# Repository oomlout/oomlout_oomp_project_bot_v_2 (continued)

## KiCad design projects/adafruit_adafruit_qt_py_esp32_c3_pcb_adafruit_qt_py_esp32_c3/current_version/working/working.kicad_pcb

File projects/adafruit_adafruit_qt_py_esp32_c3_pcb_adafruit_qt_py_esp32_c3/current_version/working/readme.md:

# adafruit_qt_py_esp32_c3_pcb
 
## summary 
* id: adafruit_adafruit_qt_py_esp32_c3_pcb_adafruit_qt_py_esp32_c3
* user: adafruit
* name: adafruit_qt_py_esp32_c3_pcb
* board: adafruit_qt_py_esp32_c3
* repo: https://github.com/adafruit/Adafruit-QT-Py-ESP32-C3-PCB

* src_file_repo_sch: 
* src_file_repo_sch_link: https://github.com/adafruit/Adafruit-QT-Py-ESP32-C3-PCB/tree/main/
* full details link: https://github.com/oomlout/oomlout_oomp_project_bot_v_2/tree/main/projects/adafruit_adafruit_qt_py_esp32_c3_pcb_adafruit_qt_py_esp32_c3/current_version/working  

## schematic  
  
[schematic (pdf)](working_schematic.pdf) 

## pcb  

[board (pdf)](working.pdf)  

## working_bom
| Id | Designator | Footprint | Quantity | Designation | Supplier and ref |  | None | 
| --- | --- | --- | --- | --- | --- | --- | --- | 
| 1 | C8,C1,C6 | 0805-NO | 3 | 22uF |  |  | [''] | 
| 2 | JP3,JP1 | 1X07_CASTEL | 2 |  |  |  | [''] | 
| 3 | Q2 | BTN_KMR2_SLIM | 1 | reset |  |  | [''] | 
| 4 | LED1 | SK6805_1515 | 1 | WS2812B_SK6805_1515 |  |  | [''] | 
| 5 | U1 | SOT23-5 | 1 | AP2112K-3.3 |  |  | [''] | 
| 6 | R5,R6 | _0402NO | 2 | 5.1K |  |  | [''] | 
| 7 | U$3 | QTPYC3_TOP | 1 |  |  |  | [''] | 
| 8 | X6 | USB_C_CUSB31-CFM2AX-01-X | 1 | USB TYPE C |  |  | [''] | 
| 9 | Q1 | BTN_KMR2_4.6X2.8 | 1 | BOOT0 |  |  | [''] | 
| 10 | U$8,U$6 | FIDUCIAL_1MM | 2 | FIDUCIAL_1MM |  |  | [''] | 
| 11 | X1 | ANT_2450AT18B100 | 1 | 2.4GHz |  |  | [''] | 
| 12 | CONN1 | JST_SH4_SKINNY | 1 | STEMMA_I2C_QTSKINNY |  |  | [''] | 
| 13 | C14,C4,C10 | _0402NO | 3 | 0.1uF |  |  | [''] | 
| 14 | GND0 | TESTPOINT_MINUS_1X3MM | 1 |  |  |  | [''] | 
| 15 | C3,C11,C2,C15 | _0402NO | 4 | 1uF |  |  | [''] | 
| 16 | SWC1,SWC2 | B1,27 | 2 | TPB1,27 |  |  | [''] | 
| 17 | L1 | _0402 | 1 | 2nH |  |  | [''] | 
| 18 | R3 | _0402NO | 1 | 0 |  |  | [''] | 
| 19 | R1,R2 | _0402NO | 2 | 10K |  |  | [''] | 
| 20 | VBAT0 | TESTPOINT_PLUS_1X3MM | 1 |  |  |  | [''] | 
| 21 | C16 | _0402NO | 1 | 0.01uF |  |  | [''] | 
| 22 | C18,C17 | _0402NO | 2 | 16pF |  |  | [''] | 
| 23 | Y1 | CRYSTAL_2X1.6 | 1 | 40MHz |  |  | [''] | 
| 24 | L2 | _0402 | 1 | 0 ohm |  |  | [''] | 
| 25 | U$18 | QTPYC3_BOT | 1 |  |  |  | [''] | 
| 26 | U$12 | PCBFEAT-REV-040 | 1 |  |  |  | [''] | 
| 27 | U2 | QFN32_5MM | 1 | ESP32-C3FH4 |  |  | [''] | 
| 28 | D1,D2 | SOD-323_MINI | 2 |   NSR0320 |  |  | [''] | 
| 29 | C9,C7 | _0402NO | 2 | TBD |  |  | [''] | 
| 30 | R7 | _0603MP_TWO6MIL | 1 | 10K |  |  | [''] | 
| 31 | R4 | _0402NO | 1 | 1k |  |  | [''] | 

## bom_schematic
| Ref | Qnty | Value | Cmp name | Footprint | Description | Vendor | DNP | 
| --- | --- | --- | --- | --- | --- | --- | --- | 
| C1, C6, C8 | 3 | 22uF | CAP_CERAMIC0805-NOOUTLINE | working:0805-NO |  |  |  | 
| C2, C3, C11, C15 | 4 | 1uF | CAP_CERAMIC_0402NO | working:_0402NO |  |  |  | 
| C4, C10, C14 | 3 | 0.1uF | CAP_CERAMIC_0402NO | working:_0402NO |  |  |  | 
| C7, C9 | 2 | TBD | CAP_CERAMIC_0402NO | working:_0402NO |  |  |  | 
| C16 | 1 | 0.01uF | CAP_CERAMIC_0402NO | working:_0402NO |  |  |  | 
| C17, C18 | 2 | 16pF | CAP_CERAMIC_0402NO | working:_0402NO |  |  |  | 
| CONN1 | 1 | STEMMA_I2C_QTSKINNY | STEMMA_I2C_QTSKINNY | working:JST_SH4_SKINNY |  |  |  | 
| D1, D2 | 2 |   NSR0320 | DIODE_SOD323MINI | working:SOD-323_MINI |  |  |  | 
| GND0 | 1 | TESTPOINT_MINUS | TESTPOINT_MINUS | working:TESTPOINT_MINUS_1X3MM |  |  |  | 
| JP1, JP3 | 2 | HEADER-1X7_CASTEL | HEADER-1X7_CASTEL | working:1X07_CASTEL |  |  |  | 
| L1 | 1 | 2nH | INDUCTOR_0402 | working:_0402 |  |  |  | 
| L2 | 1 | 0 ohm | INDUCTOR_0402 | working:_0402 |  |  |  | 
| LED1 | 1 | WS2812B_SK6805_1515 | WS2812B_SK6805_1515 | working:SK6805_1515 |  |  |  | 
| Q1 | 1 | BOOT0 | SWITCH_TACT_SMT4.6X2.8 | working:BTN_KMR2_4.6X2.8 |  |  |  | 
| Q2 | 1 | reset | SWITCH_TACT_SMT_KMR2SLIM | working:BTN_KMR2_SLIM |  |  |  | 
| R1, R2 | 2 | 10K | RESISTOR_0402NO | working:_0402NO |  |  |  | 
| R3 | 1 | 0 | RESISTOR_0402NO | working:_0402NO |  |  |  | 
| R4 | 1 | 1k | RESISTOR_0402NO | working:_0402NO |  |  |  | 
| R5, R6 | 2 | 5.1K | RESISTOR_0402NO | working:_0402NO |  |  |  | 
| R7 | 1 | 10K | RESISTOR_TWO6MIL | working:_0603MP_TWO6MIL |  |  |  | 
| SWC1, SWC2 | 2 | TPB1,27 | TPB1,27 | working:B1,27 |  |  |  | 
| U1 | 1 | AP2112K-3.3 | VREG_SOT23-5 | working:SOT23-5 |  |  |  | 
| U2 | 1 | ESP32-C3FH4 | ESP32-C3FH4 | working:QFN32_5MM |  |  |  | 
| U$6, U$8 | 2 | FIDUCIAL_1MM | FIDUCIAL_1MM | working:FIDUCIAL_1MM |  |  |  | 
| VBAT0 | 1 | TESTPOINT_PLUS13 | TESTPOINT_PLUS13 | working:TESTPOINT_PLUS_1X3MM |  |  |  | 
| X1 | 1 | 2.4GHz | ANTENNA_JOHANSON_2450AT18B100 | working:ANT_2450AT18B100 |  |  |  | 
| X6 | 1 | USB TYPE C | USB_C | working:USB_C_CUSB31-CFM2AX-01-X |  |  |  | 
| Y1 | 1 | 40MHz | CRYSTAL_2X1.6MM | working:CRYSTAL_2X1.6 |  |  |  |

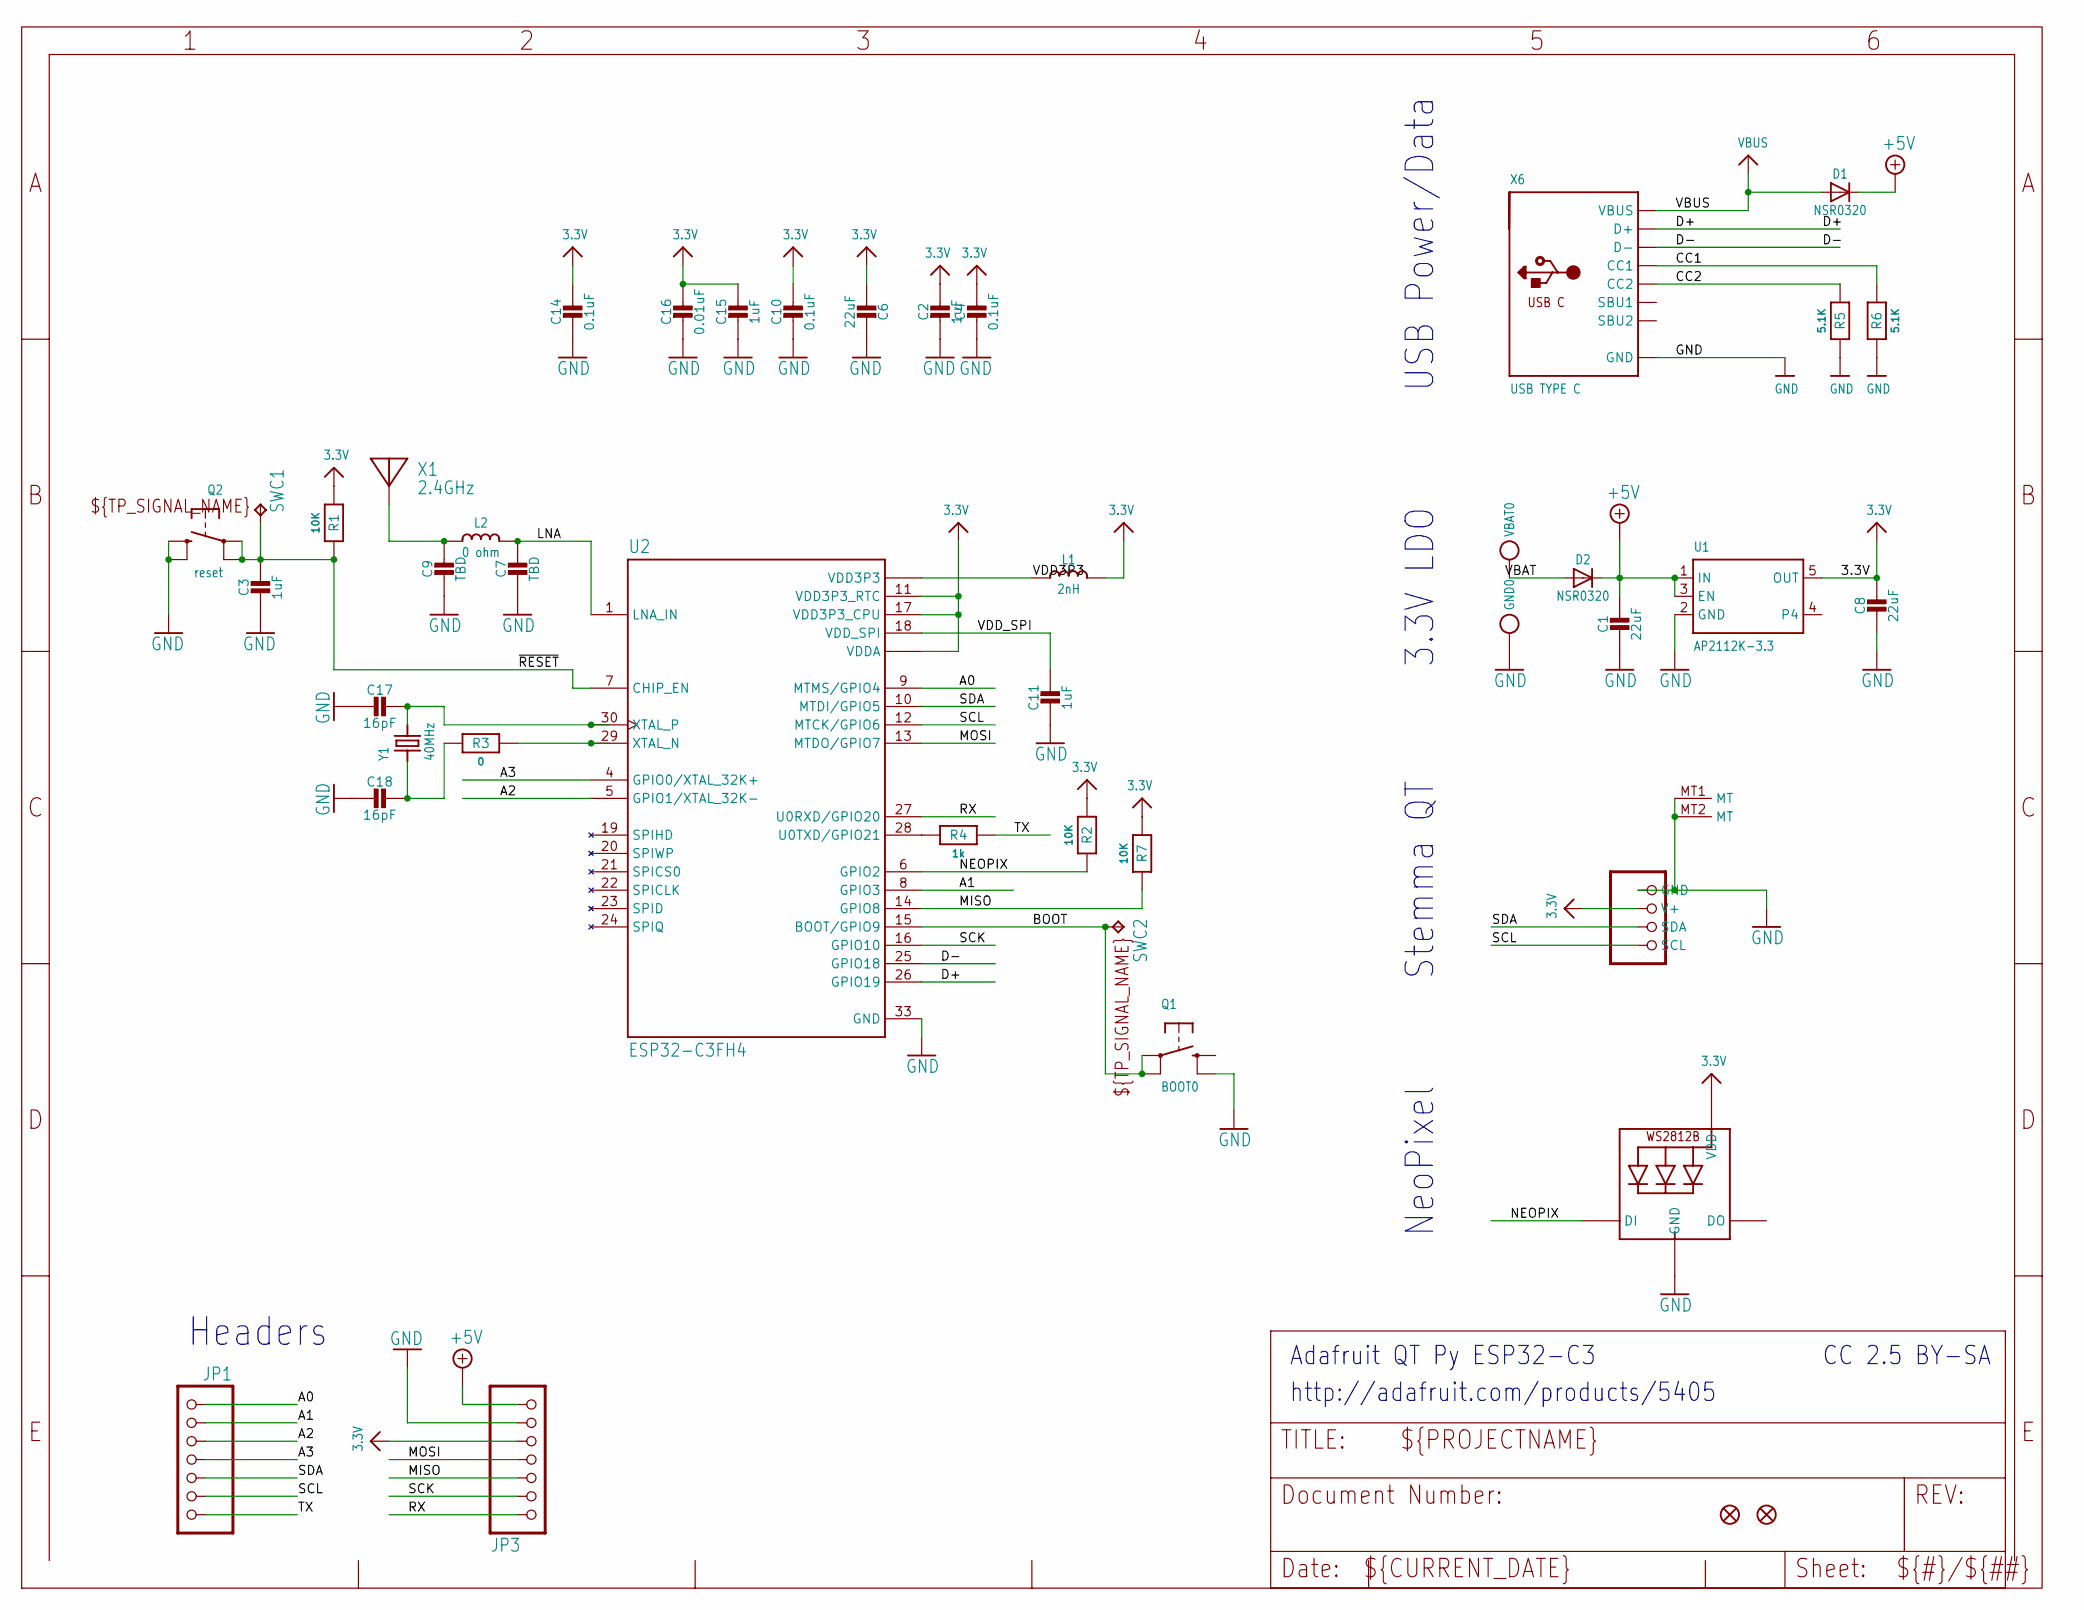
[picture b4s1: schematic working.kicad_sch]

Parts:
C1, C6, C8: 22uF; 0805-NO
C2, C3, C11, C15: 1uF; _0402NO
C4, C10, C14: 0.1uF; _0402NO
C7, C9: TBD; _0402NO
C16: 0.01uF; _0402NO
C17, C18: 16pF; _0402NO
CONN1: STEMMA_I2C_QTSKINNY; JST_SH4_SKINNY
D1, D2: NSR0320; SOD-323_MINI
GND0: TESTPOINT_MINUS; TESTPOINT_MINUS_1X3MM
JP1, JP3: HEADER-1X7_CASTEL; 1X07_CASTEL
L1: 2nH; _0402
L2: 0 ohm; _0402
LED1: WS2812B_SK6805_1515; SK6805_1515
Q1: BOOT0; BTN_KMR2_4.6X2.8
Q2: reset; BTN_KMR2_SLIM
R1, R2: 10K; _0402NO
R3: 0; _0402NO
R4: 1k; _0402NO
R5, R6: 5.1K; _0402NO
R7: 10K; _0603MP_TWO6MIL
SWC1, SWC2: TPB1,27; B1,27
U1: AP2112K-3.3; SOT23-5
U2: ESP32-C3FH4; QFN32_5MM
U$6, U$8: FIDUCIAL_1MM
VBAT0: TESTPOINT_PLUS13; TESTPOINT_PLUS_1X3MM
X1: 2.4GHz; ANT_2450AT18B100
X6: USB TYPE C; USB_C_CUSB31-CFM2AX-01-X
Y1: 40MHz; CRYSTAL_2X1.6

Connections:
3.3V: C2.1, C4.1, C6.1, C8.1, C10.1, C14.1, C15.1, C16.1, CONN1.2 (V+), JP3.5, JP3.5C (5), L1.1, LED1.2 (VDD), R1.1, R2.1, R7.1, U1.5 (OUT), U2.11 (VDD3P3_RTC), U2.17 (VDD3P3_CPU), U2.31 (VDDA), U2.32 (VDDA)
+5V: C1.1, D1.C, D2.C, JP3.7, JP3.7C (7), U1.1 (IN), U1.3 (EN)
A0: JP1.1, JP1.1C (1), U2.9 (MTMS/GPIO4)
A1: JP1.2, JP1.2C (2), U2.8 (GPIO3)
A2: JP1.3, JP1.3C (3), U2.5 (GPIO1/XTAL_32K-)
A3: JP1.4, JP1.4C (4), U2.4 (GPIO0/XTAL_32K+)
BOOT: Q1.A, Q1.A' (P1), SWC2.TP, U2.15 (BOOT/GPIO9)
CC1: R6.2, X6.A5 (CC1)
CC2: R5.2, X6.B5 (CC2)
D+: U2.26 (GPIO19), X6.A6 (D+), X6.B6 (D+)
D-: U2.25 (GPIO18), X6.A7 (D-), X6.B7 (D-)
GND: C1.2, C2.2, C3.2, C4.2, C6.2, C7.2, C8.2, C9.2, C10.2, C11.2, C14.2, C15.2, C16.2, C17.2, C18.2, CONN1.1 (GND), CONN1.MT1 (MT), CONN1.MT2 (MT), GND0.P$1, JP3.6, JP3.6C (6), LED1.4 (GND), Q1.B' (S1), Q2.B (S), Q2.B' (S1), R5.1, R6.1, U1.2 (GND), U2.33 (GND), X6.A1B12 (GND), X6.B1A12 (GND)
LNA: C7.1, L2.2, U2.1 (LNA_IN)
MISO: JP3.3, JP3.3C (3), R7.2, U2.14 (GPIO8)
MOSI: JP3.4, JP3.4C (4), U2.13 (MTDO/GPIO7)
unnamed: R4.1, U2.28 (U0TXD/GPIO21)
unnamed: C9.1, L2.1, X1.FP
unnamed: R3.2, U2.29 (XTAL_N)
unnamed: C17.1, U2.30 (XTAL_P), Y1.3 (2)
unnamed: C18.1, R3.1, Y1.1
NEOPIX: LED1.1 (DI), R2.2, U2.6 (GPIO2)
RX: JP3.1, JP3.1C (1), U2.27 (U0RXD/GPIO20)
SCK: JP3.2, JP3.2C (2), U2.16 (GPIO10)
SCL: CONN1.4 (SCL), JP1.6, JP1.6C (6), U2.12 (MTCK/GPIO6)
SDA: CONN1.3 (SDA), JP1.5, JP1.5C (5), U2.10 (MTDI/GPIO5)
TX: JP1.7, JP1.7C (7), R4.2
VBAT: D2.A, VBAT0.P$1
VBUS: D1.A, X6.A4B9 (VBUS), X6.B4A9 (VBUS)
VDD3P3: L1.2, U2.2 (VDD3P3), U2.3 (VDD3P3)
VDD_SPI: C11.1, U2.18 (VDD_SPI)
~RESET: C3.1, Q2.A, Q2.A' (P1), R1.2, SWC1.TP, U2.7 (CHIP_EN)

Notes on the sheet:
Headers
Adafruit QT Py ESP32-C3
http://adafruit.com/products/5405
CC 2.5 BY-SA
USB Power/Data
NeoPixel
Stemma QT
3.3V LDO

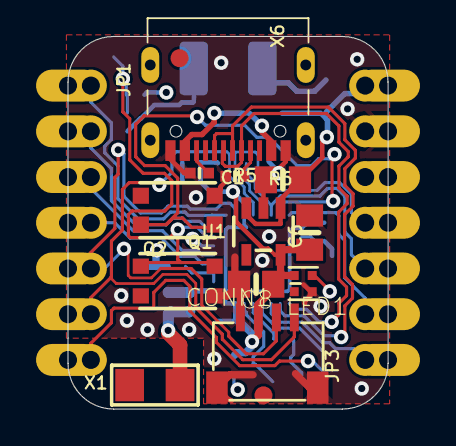
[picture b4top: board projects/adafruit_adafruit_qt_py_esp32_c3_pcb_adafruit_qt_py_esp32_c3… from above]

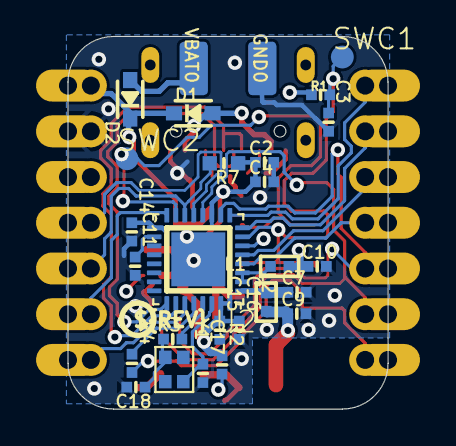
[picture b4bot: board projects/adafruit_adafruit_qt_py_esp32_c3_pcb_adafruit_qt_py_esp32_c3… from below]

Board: 4 copper layers, 17.8 x 20.7 mm, 46 parts (29 on the bottom side), 31 nets.

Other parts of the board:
U$3: QTPYC3_TOP
U$12: PCBFEAT-REV-040
U$18: QTPYC3_BOT

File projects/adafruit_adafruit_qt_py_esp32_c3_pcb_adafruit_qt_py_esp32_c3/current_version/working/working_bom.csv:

"Id";"Designator";"Footprint";"Quantity";"Designation";"Supplier and ref";
1;"C8,C1,C6";"0805-NO";3;"22uF";;;
2;"JP3,JP1";"1X07_CASTEL";2;"";;;
3;"Q2";"BTN_KMR2_SLIM";1;"reset";;;
4;"LED1";"SK6805_1515";1;"WS2812B_SK6805_1515";;;
5;"U1";"SOT23-5";1;"AP2112K-3.3";;;
6;"R5,R6";"_0402NO";2;"5.1K";;;
7;"U$3";"QTPYC3_TOP";1;"";;;
8;"X6";"USB_C_CUSB31-CFM2AX-01-X";1;"USB TYPE C";;;
9;"Q1";"BTN_KMR2_4.6X2.8";1;"BOOT0";;;
10;"U$8,U$6";"FIDUCIAL_1MM";2;"FIDUCIAL_1MM";;;
11;"X1";"ANT_2450AT18B100";1;"2.4GHz";;;
12;"CONN1";"JST_SH4_SKINNY";1;"STEMMA_I2C_QTSKINNY";;;
13;"C14,C4,C10";"_0402NO";3;"0.1uF";;;
14;"GND0";"TESTPOINT_MINUS_1X3MM";1;"";;;
15;"C3,C11,C2,C15";"_0402NO";4;"1uF";;;
16;"SWC1,SWC2";"B1,27";2;"TPB1,27";;;
17;"L1";"_0402";1;"2nH";;;
18;"R3";"_0402NO";1;"0";;;
19;"R1,R2";"_0402NO";2;"10K";;;
20;"VBAT0";"TESTPOINT_PLUS_1X3MM";1;"";;;
21;"C16";"_0402NO";1;"0.01uF";;;
22;"C18,C17";"_0402NO";2;"16pF";;;
23;"Y1";"CRYSTAL_2X1.6";1;"40MHz";;;
24;"L2";"_0402";1;"0 ohm";;;
25;"U$18";"QTPYC3_BOT";1;"";;;
26;"U$12";"PCBFEAT-REV-040";1;"";;;
27;"U2";"QFN32_5MM";1;"ESP32-C3FH4";;;
28;"D1,D2";"SOD-323_MINI";2;"  NSR0320";;;
29;"C9,C7";"_0402NO";2;"TBD";;;
30;"R7";"_0603MP_TWO6MIL";1;"10K";;;
31;"R4";"_0402NO";1;"1k";;;

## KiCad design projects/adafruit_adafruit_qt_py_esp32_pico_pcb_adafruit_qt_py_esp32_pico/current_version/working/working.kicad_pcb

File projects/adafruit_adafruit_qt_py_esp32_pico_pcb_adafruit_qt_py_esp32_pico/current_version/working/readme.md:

# adafruit_qt_py_esp32_pico_pcb
 
## summary 
* id: adafruit_adafruit_qt_py_esp32_pico_pcb_adafruit_qt_py_esp32_pico
* user: adafruit
* name: adafruit_qt_py_esp32_pico_pcb
* board: adafruit_qt_py_esp32_pico
* repo: https://github.com/adafruit/Adafruit-QT-Py-ESP32-Pico-PCB

* src_file_repo_sch: 
* src_file_repo_sch_link: https://github.com/adafruit/Adafruit-QT-Py-ESP32-Pico-PCB/tree/main/
* full details link: https://github.com/oomlout/oomlout_oomp_project_bot_v_2/tree/main/projects/adafruit_adafruit_qt_py_esp32_pico_pcb_adafruit_qt_py_esp32_pico/current_version/working  

## schematic  
  
[schematic (pdf)](working_schematic.pdf) 

## pcb  

[board (pdf)](working.pdf)  

## working_bom
| Id | Designator | Footprint | Quantity | Designation | Supplier and ref |  | None | 
| --- | --- | --- | --- | --- | --- | --- | --- | 
| 1 | Q2 | BTN_KMR2_4.6X2.8 | 1 | reset |  |  | [''] | 
| 2 | R5,R6 | _0402NO | 2 | 5.1K |  |  | [''] | 
| 3 | C6,C1,C8 | 0805-NO | 3 | 22uF |  |  | [''] | 
| 4 | X6 | USB_C_CUSB31-CFM2AX-01-X | 1 | USB TYPE C |  |  | [''] | 
| 5 | X1 | ANT_2450AT18B100 | 1 | 2.4GHz |  |  | [''] | 
| 6 | U$22 | QTPY_ESP32_TOP | 1 |  |  |  | [''] | 
| 7 | JP3,JP1 | 1X07_CASTEL | 2 |  |  |  | [''] | 
| 8 | U1 | SOT23-5 | 1 | AP2112K-3.3 |  |  | [''] | 
| 9 | LED1 | SK6805_1515 | 1 | WS2812B_SK6805_1515 |  |  | [''] | 
| 10 | U$8,U$6 | FIDUCIAL_1MM | 2 | FIDUCIAL_1MM |  |  | [''] | 
| 11 | Q1 | BTN_KMR2_4.6X2.8 | 1 | BOOT0 |  |  | [''] | 
| 12 | CONN1 | JST_SH4_SKINNY | 1 | STEMMA_I2C_QTSKINNY |  |  | [''] | 
| 13 | R7,R3,R1,R2 | _0402NO | 4 | 10K |  |  | [''] | 
| 14 | VBAT0 | TESTPOINT_PLUS_1X3MM | 1 |  |  |  | [''] | 
| 15 | GND0 | TESTPOINT_MINUS_1X3MM | 1 |  |  |  | [''] | 
| 16 | C9,C7 | _0402NO | 2 | 1.2pF |  |  | [''] | 
| 17 | L2 | _0402 | 1 | 2.2nH |  |  | [''] | 
| 18 | SWC1,SWC2 | B1,27 | 2 | TPB1,27 |  |  | [''] | 
| 19 | C5 | _0402NO | 1 | .1uF |  |  | [''] | 
| 20 | D1,D2 | SOD-323_MINI | 2 |   NSR0320 |  |  | [''] | 
| 21 | R4 | _0402NO | 1 | 22K |  |  | [''] | 
| 22 | C2,C3,C12 | _0402NO | 3 | 1uF |  |  | [''] | 
| 23 | U$12 | PCBFEAT-REV-040 | 1 |  |  |  | [''] | 
| 24 | IC1 | QFN24_4MM_SMSC | 1 | CP2102N-24 |  |  | [''] | 
| 25 | C11 | _0402NO | 1 | 0.1uF |  |  | [''] | 
| 26 | X2 | QFN48_7X7 | 1 | ESP-32-PICO-V3-02 |  |  | [''] | 
| 27 | Q5 | SOT363 | 1 | DUAL NPN |  |  | [''] | 
| 28 | U$3 | QTPY_ESP32_BOT | 1 |  |  |  | [''] | 
| 29 | C19 | 0603-NO_WIDE | 1 | 1uF |  |  | [''] | 

## bom_schematic
| Ref | Qnty | Value | Cmp name | Footprint | Description | Vendor | DNP | 
| --- | --- | --- | --- | --- | --- | --- | --- | 
| C1, C6, C8 | 3 | 22uF | CAP_CERAMIC0805-NOOUTLINE | working:0805-NO |  |  |  | 
| C2, C3, C12 | 3 | 1uF | CAP_CERAMIC_0402NO | working:_0402NO |  |  |  | 
| C5 | 1 | .1uF | CAP_CERAMIC_0402NO | working:_0402NO |  |  |  | 
| C7, C9 | 2 | 1.2pF | CAP_CERAMIC_0402NO | working:_0402NO |  |  |  | 
| C11 | 1 | 0.1uF | CAP_CERAMIC_0402NO | working:_0402NO |  |  |  | 
| C19 | 1 | 1uF | CAP_CERAMIC_0603WIDE | working:0603-NO_WIDE |  |  |  | 
| CONN1 | 1 | STEMMA_I2C_QTSKINNY | STEMMA_I2C_QTSKINNY | working:JST_SH4_SKINNY |  |  |  | 
| D1, D2 | 2 |   NSR0320 | DIODE_SOD323MINI | working:SOD-323_MINI |  |  |  | 
| GND0 | 1 | TESTPOINT_MINUS | TESTPOINT_MINUS | working:TESTPOINT_MINUS_1X3MM |  |  |  | 
| IC1 | 1 | CP2102N-24 | CP2102N-24 | working:QFN24_4MM_SMSC |  |  |  | 
| JP1, JP3 | 2 | HEADER-1X7_CASTEL | HEADER-1X7_CASTEL | working:1X07_CASTEL |  |  |  | 
| L2 | 1 | 2.2nH | INDUCTOR_0402 | working:_0402 |  |  |  | 
| LED1 | 1 | WS2812B_SK6805_1515 | WS2812B_SK6805_1515 | working:SK6805_1515 |  |  |  | 
| Q1 | 1 | BOOT0 | SWITCH_TACT_SMT4.6X2.8 | working:BTN_KMR2_4.6X2.8 |  |  |  | 
| Q2 | 1 | reset | SWITCH_TACT_SMT4.6X2.8 | working:BTN_KMR2_4.6X2.8 |  |  |  | 
| Q5 | 1 | DUAL NPN | MOSFET-N_DUAL | working:SOT363 |  |  |  | 
| R1, R2, R3, R7 | 4 | 10K | RESISTOR_0402NO | working:_0402NO |  |  |  | 
| R4 | 1 | 22K | RESISTOR_0402NO | working:_0402NO |  |  |  | 
| R5, R6 | 2 | 5.1K | RESISTOR_0402NO | working:_0402NO |  |  |  | 
| SWC1, SWC2 | 2 | TPB1,27 | TPB1,27 | working:B1,27 |  |  |  | 
| U1 | 1 | AP2112K-3.3 | VREG_SOT23-5 | working:SOT23-5 |  |  |  | 
| U$6, U$8 | 2 | FIDUCIAL_1MM | FIDUCIAL_1MM | working:FIDUCIAL_1MM |  |  |  | 
| VBAT0 | 1 | TESTPOINT_PLUS13 | TESTPOINT_PLUS13 | working:TESTPOINT_PLUS_1X3MM |  |  |  | 
| X1 | 1 | 2.4GHz | ANTENNA_JOHANSON_2450AT18B100 | working:ANT_2450AT18B100 |  |  |  | 
| X2 | 1 | ESP-32-PICO-V3-02 | ESP-32-PICO-V3-02 | working:QFN48_7X7 |  |  |  | 
| X6 | 1 | USB TYPE C | USB_C | working:USB_C_CUSB31-CFM2AX-01-X |  |  |  |

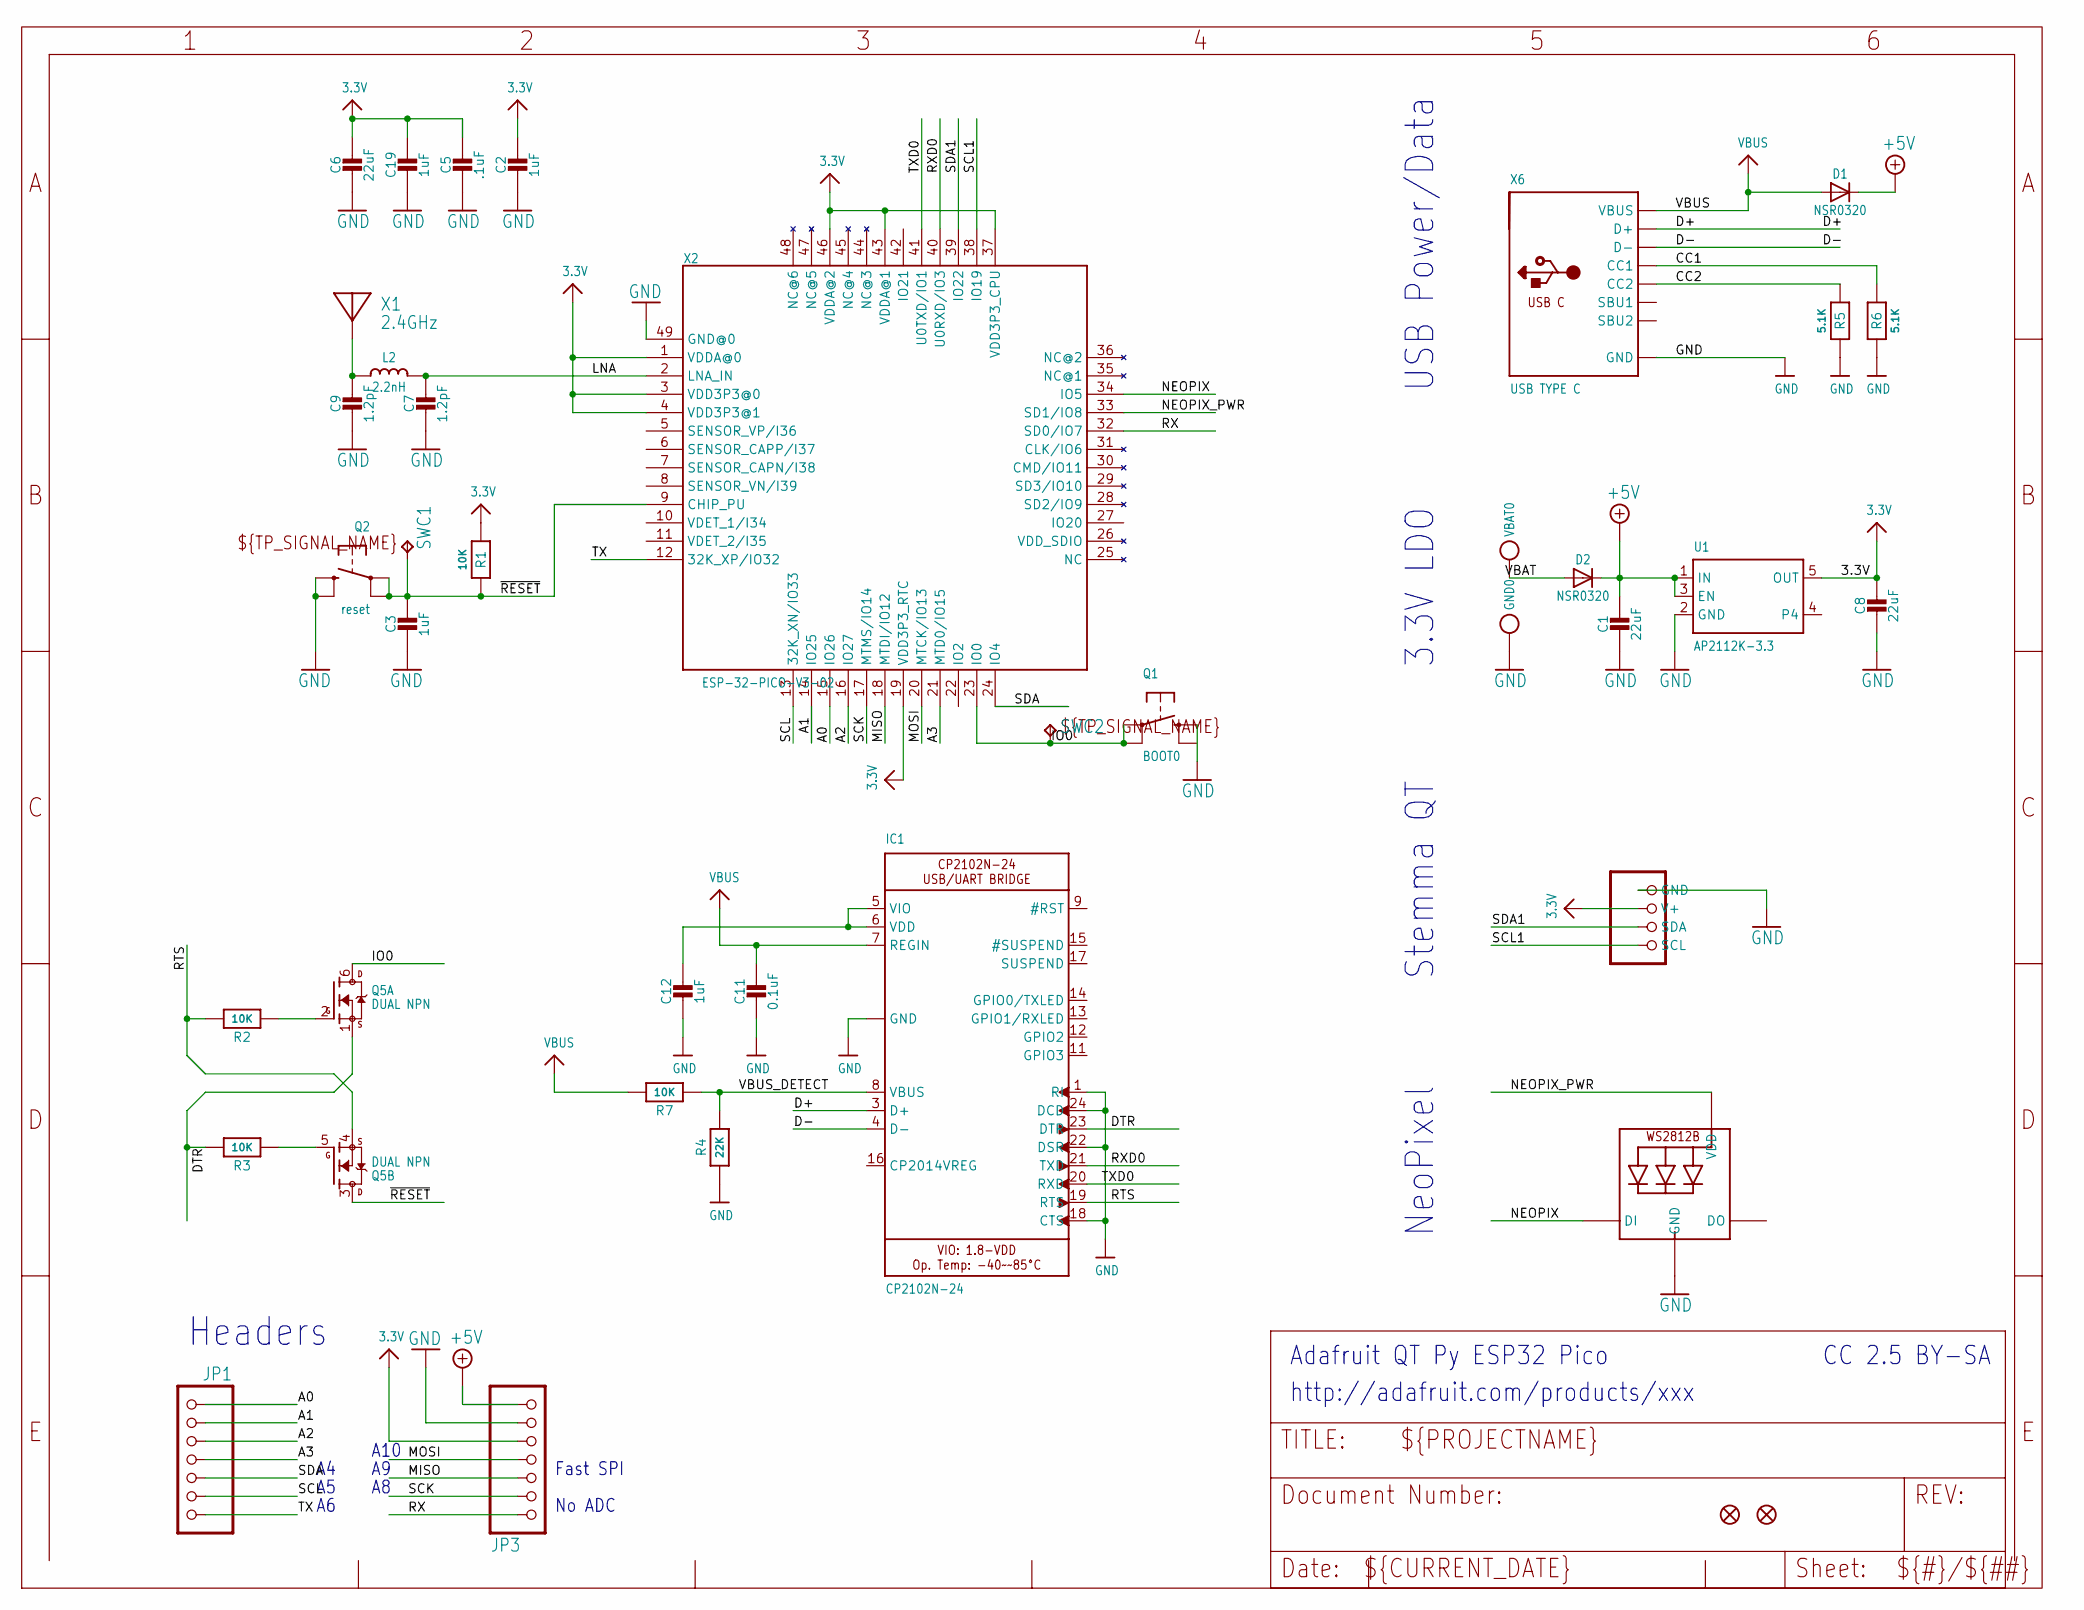
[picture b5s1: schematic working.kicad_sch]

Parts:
C1, C6, C8: 22uF; 0805-NO
C2, C3, C12: 1uF; _0402NO
C5: .1uF; _0402NO
C7, C9: 1.2pF; _0402NO
C11: 0.1uF; _0402NO
C19: 1uF; 0603-NO_WIDE
CONN1: STEMMA_I2C_QTSKINNY; JST_SH4_SKINNY
D1, D2: NSR0320; SOD-323_MINI
GND0: TESTPOINT_MINUS; TESTPOINT_MINUS_1X3MM
IC1: CP2102N-24; QFN24_4MM_SMSC
JP1, JP3: HEADER-1X7_CASTEL; 1X07_CASTEL
L2: 2.2nH; _0402
LED1: WS2812B_SK6805_1515; SK6805_1515
Q1: BOOT0; BTN_KMR2_4.6X2.8
Q2: reset; BTN_KMR2_4.6X2.8
Q5: DUAL NPN; SOT363
R1, R2, R3, R7: 10K; _0402NO
R4: 22K; _0402NO
R5, R6: 5.1K; _0402NO
SWC1, SWC2: TPB1,27; B1,27
U1: AP2112K-3.3; SOT23-5
U$6, U$8: FIDUCIAL_1MM
VBAT0: TESTPOINT_PLUS13; TESTPOINT_PLUS_1X3MM
X1: 2.4GHz; ANT_2450AT18B100
X2: ESP-32-PICO-V3-02; QFN48_7X7
X6: USB TYPE C; USB_C_CUSB31-CFM2AX-01-X

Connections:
3.3V: C2.1, C5.1, C6.1, C8.1, C19.1, CONN1.2 (V+), JP3.5, JP3.5C (5), R1.1, U1.5 (OUT), X2.1 (VDDA@0), X2.3 (VDD3P3@0), X2.4 (VDD3P3@1), X2.19 (VDD3P3_RTC), X2.37 (VDD3P3_CPU), X2.43 (VDDA@1), X2.46 (VDDA@2)
+5V: C1.1, D1.C, D2.C, JP3.7, JP3.7C (7), U1.1 (IN), U1.3 (EN)
A0: JP1.1, JP1.1C (1), X2.15 (IO26)
A1: JP1.2, JP1.2C (2), X2.14 (IO25)
A2: JP1.3, JP1.3C (3), X2.16 (IO27)
A3: JP1.4, JP1.4C (4), X2.21 (MTD0/IO15)
CC1: R6.2, X6.A5 (CC1)
CC2: R5.2, X6.B5 (CC2)
D+: IC1.3 (D+), X6.A6 (D+), X6.B6 (D+)
D-: IC1.4 (D-), X6.A7 (D-), X6.B7 (D-)
DTR: IC1.23 (DTR), Q5.1 (S), R3.2
GND: C1.2, C2.2, C3.2, C5.2, C6.2, C7.2, C8.2, C9.2, C11.2, C12.2, C19.2, CONN1.1 (GND), GND0.P$1, IC1.1 (RI), IC1.2 (GND), IC1.18 (CTS), IC1.22 (DSR), IC1.24 (DCD), IC1.THERM (GND), JP3.6, JP3.6C (6), LED1.4 (GND), Q1.B (S), Q1.B' (S1), Q2.B (S), Q2.B' (S1), R4.1, R5.1, R6.1, U1.2 (GND), X2.49 (GND@0), X6.A1B12 (GND), X6.B1A12 (GND)
IO0: Q1.A, Q1.A' (P1), Q5.6 (D), SWC2.TP, X2.23 (IO0)
LNA: C7.1, L2.2, X2.2 (LNA_IN)
MISO: JP3.3, JP3.3C (3), X2.18 (MTDI/IO12)
MOSI: JP3.4, JP3.4C (4), X2.20 (MTCK/IO13)
unnamed: C12.1, IC1.5 (VIO), IC1.6 (VDD)
unnamed: C9.1, L2.1, X1.FP
unnamed: Q5.5 (G), R3.1
unnamed: Q5.2 (G), R2.1
NEOPIX: LED1.1 (DI), X2.34 (IO5)
NEOPIX_PWR: LED1.2 (VDD), X2.33 (SD1/IO8)
RTS: IC1.19 (RTS), Q5.4 (S), R2.2
RX: JP3.1, JP3.1C (1), X2.32 (SD0/IO7)
RXD0: IC1.21 (TXD), X2.40 (U0RXD/IO3)
SCK: JP3.2, JP3.2C (2), X2.17 (MTMS/IO14)
SCL: JP1.6, JP1.6C (6), X2.13 (32K_XN/IO33)
SCL1: CONN1.4 (SCL), X2.38 (IO19)
SDA: JP1.5, JP1.5C (5), X2.24 (IO4)
SDA1: CONN1.3 (SDA), X2.39 (IO22)
TX: JP1.7, JP1.7C (7), X2.12 (32K_XP/IO32)
TXD0: IC1.20 (RXD), X2.41 (U0TXD/IO1)
VBAT: D2.A, VBAT0.P$1
VBUS: C11.1, D1.A, IC1.7 (REGIN), R7.2, X6.A4B9 (VBUS), X6.B4A9 (VBUS)
VBUS_DETECT: IC1.8 (VBUS), R4.2, R7.1
~RESET: C3.1, Q2.A, Q2.A' (P1), Q5.3 (D), R1.2, SWC1.TP, X2.9 (CHIP_PU)

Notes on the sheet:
CC 2.5 BY-SA
http://adafruit.com/products/xxx
Adafruit QT Py ESP32 Pico
Stemma QT
A10
NeoPixel
Headers
Fast SPI
3.3V LDO
USB Power/Data
No ADC

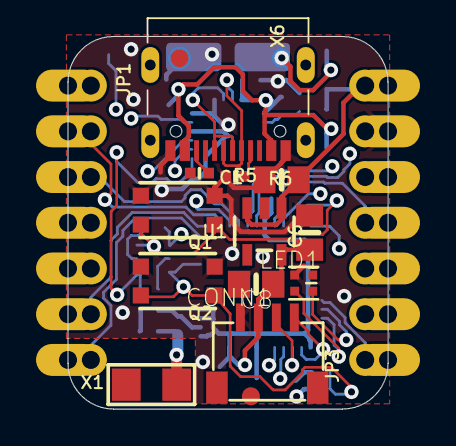
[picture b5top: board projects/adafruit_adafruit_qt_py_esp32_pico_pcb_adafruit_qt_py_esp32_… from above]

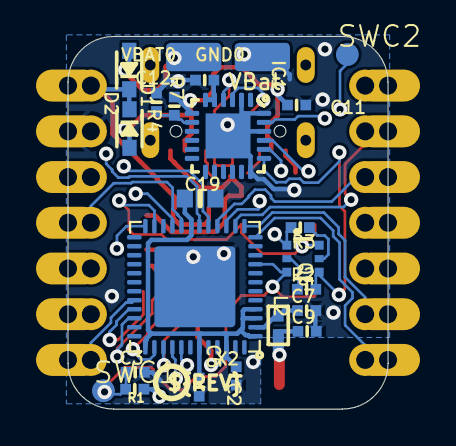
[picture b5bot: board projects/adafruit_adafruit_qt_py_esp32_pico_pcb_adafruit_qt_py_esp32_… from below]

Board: 4 copper layers, 17.8 x 20.7 mm, 42 parts (25 on the bottom side), 36 nets.

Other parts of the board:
U$3: QTPY_ESP32_BOT
U$12: PCBFEAT-REV-040
U$22: QTPY_ESP32_TOP

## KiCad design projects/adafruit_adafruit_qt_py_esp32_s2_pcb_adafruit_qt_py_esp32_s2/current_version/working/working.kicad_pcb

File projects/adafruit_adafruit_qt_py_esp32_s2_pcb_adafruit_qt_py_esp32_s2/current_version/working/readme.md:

# adafruit_qt_py_esp32_s2_pcb
 
## summary 
* id: adafruit_adafruit_qt_py_esp32_s2_pcb_adafruit_qt_py_esp32_s2
* user: adafruit
* name: adafruit_qt_py_esp32_s2_pcb
* board: adafruit_qt_py_esp32_s2
* repo: https://github.com/adafruit/Adafruit-QT-Py-ESP32-S2-PCB

* src_file_repo_sch: 
* src_file_repo_sch_link: https://github.com/adafruit/Adafruit-QT-Py-ESP32-S2-PCB/tree/main/
* full details link: https://github.com/oomlout/oomlout_oomp_project_bot_v_2/tree/main/projects/adafruit_adafruit_qt_py_esp32_s2_pcb_adafruit_qt_py_esp32_s2/current_version/working  

## schematic  
  
[schematic (pdf)](working_schematic.pdf) 

## pcb  

[board (pdf)](working.pdf)  

## working_bom
| Id | Designator | Footprint | Quantity | Designation | Supplier and ref |  | None | 
| --- | --- | --- | --- | --- | --- | --- | --- | 
| 1 | JP3,JP1 | 1X07_CASTEL | 2 |  |  |  | [''] | 
| 2 | R5,R6 | _0402NO | 2 | 5.1K |  |  | [''] | 
| 3 | C1,C6,C8 | 0805-NO | 3 | 22uF |  |  | [''] | 
| 4 | U$6,U$8 | FIDUCIAL_1MM | 2 | FIDUCIAL_1MM |  |  | [''] | 
| 5 | X6 | USB_C_CUSB31-CFM2AX-01-X | 1 | USB TYPE C |  |  | [''] | 
| 6 | Q1 | BTN_KMR2_4.6X2.8 | 1 | BOOT0 |  |  | [''] | 
| 7 | CONN1 | JST_SH4_SKINNY | 1 | STEMMA_I2C_QTSKINNY |  |  | [''] | 
| 8 | U1 | SOT23-5 | 1 | AP2112K-3.3 |  |  | [''] | 
| 9 | Q2 | BTN_KMR2_4.6X2.8 | 1 | reset |  |  | [''] | 
| 10 | U$13 | QTPY_ESP32_TOP | 1 |  |  |  | [''] | 
| 11 | LED1 | SK6805_1515 | 1 | WS2812B_SK6805_1515 |  |  | [''] | 
| 12 | X1 | ANT_2450AT18B100 | 1 |  |  |  | [''] | 
| 13 | D1,D2 | SOD-323_MINI | 2 |   NSR0320 |  |  | [''] | 
| 14 | U$12 | PCBFEAT-REV-040 | 1 |  |  |  | [''] | 
| 15 | C19,C3,C5,C13,C2,C15,C20 | _0402NO | 7 | 1uF |  |  | [''] | 
| 16 | C17,C18 | _0402NO | 2 | 16pF |  |  | [''] | 
| 17 | C16 | _0402NO | 1 | 100pF |  |  | [''] | 
| 18 | U$7 | QTPYS2_BOT | 1 |  |  |  | [''] | 
| 19 | L1 | _0402 | 1 | 2nH |  |  | [''] | 
| 20 | C9,C7 | _0402NO | 2 | TBD |  |  | [''] | 
| 21 | U$15 | QFN56_7X7 | 1 | ESP32-S2QFN54 |  |  | [''] | 
| 22 | VBAT0 | TESTPOINT_PLUS_1X3MM | 1 |  |  |  | [''] | 
| 23 | GND0 | TESTPOINT_MINUS_1X3MM | 1 |  |  |  | [''] | 
| 24 | R2,R1 | _0402NO | 2 | 10K |  |  | [''] | 
| 25 | C11,C10,C4,C12,C14 | _0402NO | 5 | 0.1uF |  |  | [''] | 
| 26 | L2 | _0402 | 1 | 0 ohm |  |  | [''] | 
| 27 | SWC1,SWC2 | B1,27 | 2 | TPB1,27 |  |  | [''] | 
| 28 | Y1 | CRYSTAL_2X1.6 | 1 | 40MHz |  |  | [''] | 
| 29 | R17 | _0402NO | 1 | 1Meg |  |  | [''] | 
| 30 | R3 | _0402NO | 1 | 0 |  |  | [''] | 

## bom_schematic
| Ref | Qnty | Value | Cmp name | Footprint | Description | Vendor | DNP | 
| --- | --- | --- | --- | --- | --- | --- | --- | 
| C1, C6, C8 | 3 | 22uF | CAP_CERAMIC0805-NOOUTLINE | working:0805-NO |  |  |  | 
| C2, C3, C5, C13, C15, C19, C20 | 7 | 1uF | CAP_CERAMIC_0402NO | working:_0402NO |  |  |  | 
| C4, C10, C11, C12, C14 | 5 | 0.1uF | CAP_CERAMIC_0402NO | working:_0402NO |  |  |  | 
| C7, C9 | 2 | TBD | CAP_CERAMIC_0402NO | working:_0402NO |  |  |  | 
| C16 | 1 | 100pF | CAP_CERAMIC_0402NO | working:_0402NO |  |  |  | 
| C17, C18 | 2 | 16pF | CAP_CERAMIC_0402NO | working:_0402NO |  |  |  | 
| CONN1 | 1 | STEMMA_I2C_QTSKINNY | STEMMA_I2C_QTSKINNY | working:JST_SH4_SKINNY |  |  |  | 
| D1, D2 | 2 |   NSR0320 | DIODE_SOD323MINI | working:SOD-323_MINI |  |  |  | 
| GND0 | 1 | TESTPOINT_MINUS | TESTPOINT_MINUS | working:TESTPOINT_MINUS_1X3MM |  |  |  | 
| JP1, JP3 | 2 | HEADER-1X7_CASTEL | HEADER-1X7_CASTEL | working:1X07_CASTEL |  |  |  | 
| L1 | 1 | 2nH | INDUCTOR_0402 | working:_0402 |  |  |  | 
| L2 | 1 | 0 ohm | INDUCTOR_0402 | working:_0402 |  |  |  | 
| LED1 | 1 | WS2812B_SK6805_1515 | WS2812B_SK6805_1515 | working:SK6805_1515 |  |  |  | 
| Q1 | 1 | BOOT0 | SWITCH_TACT_SMT4.6X2.8 | working:BTN_KMR2_4.6X2.8 |  |  |  | 
| Q2 | 1 | reset | SWITCH_TACT_SMT4.6X2.8 | working:BTN_KMR2_4.6X2.8 |  |  |  | 
| R1, R2 | 2 | 10K | RESISTOR_0402NO | working:_0402NO |  |  |  | 
| R3 | 1 | 0 | RESISTOR_0402NO | working:_0402NO |  |  |  | 
| R5, R6 | 2 | 5.1K | RESISTOR_0402NO | working:_0402NO |  |  |  | 
| R17 | 1 | 1Meg | RESISTOR_0402NO | working:_0402NO |  |  |  | 
| SWC1, SWC2 | 2 | TPB1,27 | TPB1,27 | working:B1,27 |  |  |  | 
| U1 | 1 | AP2112K-3.3 | VREG_SOT23-5 | working:SOT23-5 |  |  |  | 
| U$6, U$8 | 2 | FIDUCIAL_1MM | FIDUCIAL_1MM | working:FIDUCIAL_1MM |  |  |  | 
| U$15 | 1 | ESP32-S2QFN54 | ESP32-S2QFN54 | working:QFN56_7X7 |  |  |  | 
| VBAT0 | 1 | TESTPOINT_PLUS13 | TESTPOINT_PLUS13 | working:TESTPOINT_PLUS_1X3MM |  |  |  | 
| X1 | 1 | ANTENNA_JOHANSON_2450AT18B100 | ANTENNA_JOHANSON_2450AT18B100 | working:ANT_2450AT18B100 |  |  |  | 
| X6 | 1 | USB TYPE C | USB_C | working:USB_C_CUSB31-CFM2AX-01-X |  |  |  | 
| Y1 | 1 | 40MHz | CRYSTAL_2X1.6MM | working:CRYSTAL_2X1.6 |  |  |  |

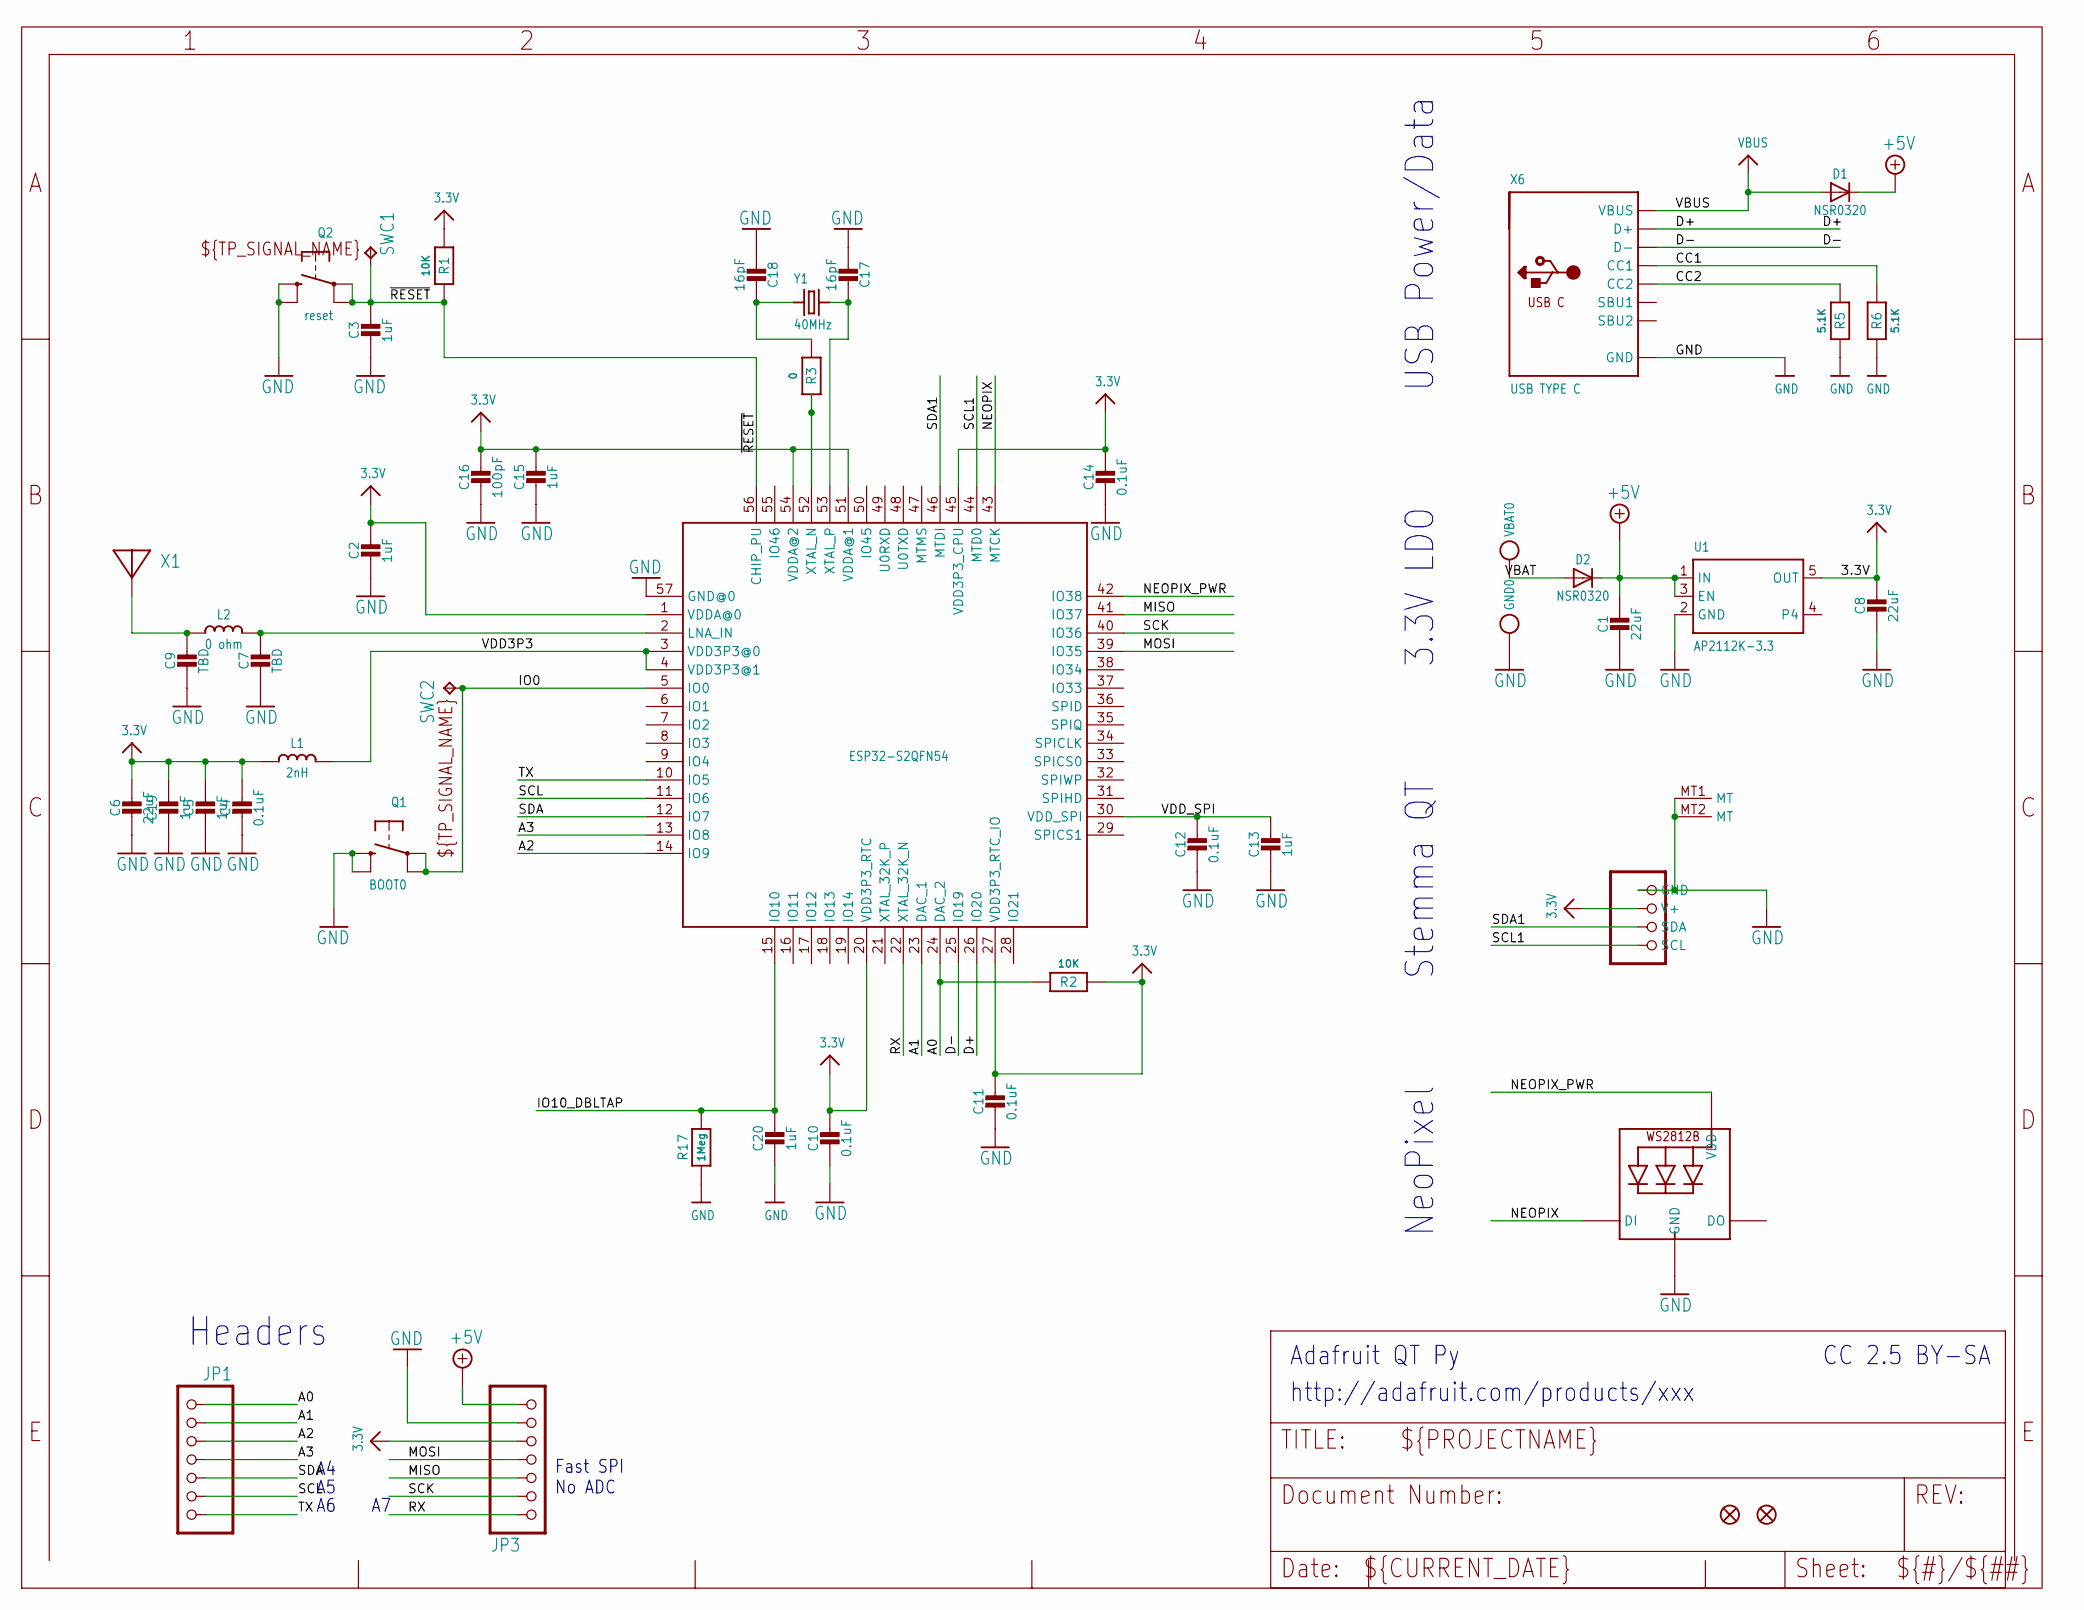
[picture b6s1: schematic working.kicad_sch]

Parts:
C1, C6, C8: 22uF; 0805-NO
C2, C3, C5, C13, C15, C19, C20: 1uF; _0402NO
C4, C10, C11, C12, C14: 0.1uF; _0402NO
C7, C9: TBD; _0402NO
C16: 100pF; _0402NO
C17, C18: 16pF; _0402NO
CONN1: STEMMA_I2C_QTSKINNY; JST_SH4_SKINNY
D1, D2: NSR0320; SOD-323_MINI
GND0: TESTPOINT_MINUS; TESTPOINT_MINUS_1X3MM
JP1, JP3: HEADER-1X7_CASTEL; 1X07_CASTEL
L1: 2nH; _0402
L2: 0 ohm; _0402
LED1: WS2812B_SK6805_1515; SK6805_1515
Q1: BOOT0; BTN_KMR2_4.6X2.8
Q2: reset; BTN_KMR2_4.6X2.8
R1, R2: 10K; _0402NO
R3: 0; _0402NO
R5, R6: 5.1K; _0402NO
R17: 1Meg; _0402NO
SWC1, SWC2: TPB1,27; B1,27
U1: AP2112K-3.3; SOT23-5
U$6, U$8: FIDUCIAL_1MM
U$15: ESP32-S2QFN54; QFN56_7X7
VBAT0: TESTPOINT_PLUS13; TESTPOINT_PLUS_1X3MM
X1: ANTENNA_JOHANSON_2450AT18B100; ANT_2450AT18B100
X6: USB TYPE C; USB_C_CUSB31-CFM2AX-01-X
Y1: 40MHz; CRYSTAL_2X1.6

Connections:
3.3V: C2.1, C4.1, C5.1, C6.1, C8.1, C10.1, C11.1, C14.1, C15.1, C16.1, C19.1, CONN1.2 (V+), JP3.5, JP3.5C (5), L1.1, R1.1, R2.1, U1.5 (OUT), U$15.1 (VDDA@0), U$15.20 (VDD3P3_RTC), U$15.27 (VDD3P3_RTC_IO), U$15.45 (VDD3P3_CPU), U$15.51 (VDDA@1), U$15.54 (VDDA@2)
+5V: C1.1, D1.C, D2.C, JP3.7, JP3.7C (7), U1.1 (IN), U1.3 (EN)
A0: JP1.1, JP1.1C (1), R2.2, U$15.24 (DAC_2)
A1: JP1.2, JP1.2C (2), U$15.23 (DAC_1)
A2: JP1.3, JP1.3C (3), U$15.14 (IO9)
A3: JP1.4, JP1.4C (4), U$15.13 (IO8)
CC1: R6.2, X6.A5 (CC1)
CC2: R5.2, X6.B5 (CC2)
D+: U$15.26 (IO20), X6.A6 (D+), X6.B6 (D+)
D-: U$15.25 (IO19), X6.A7 (D-), X6.B7 (D-)
GND: C1.2, C2.2, C3.2, C4.2, C5.2, C6.2, C7.2, C8.2, C9.2, C10.2, C11.2, C12.2, C13.2, C14.2, C15.2, C16.2, C17.2, C18.2, C19.2, C20.2, CONN1.1 (GND), CONN1.MT1 (MT), CONN1.MT2 (MT), GND0.P$1, JP3.6, JP3.6C (6), LED1.4 (GND), Q1.B (S), Q1.B' (S1), Q2.B (S), Q2.B' (S1), R5.1, R6.1, R17.1, U1.2 (GND), U$15.57 (GND@0), X6.A1B12 (GND), X6.B1A12 (GND)
IO0: Q1.A, Q1.A' (P1), SWC2.TP, U$15.5 (IO0)
IO10_DBLTAP: C20.1, R17.2, U$15.15 (IO10)
MISO: JP3.3, JP3.3C (3), U$15.41 (IO37)
MOSI: JP3.4, JP3.4C (4), U$15.39 (IO35)
unnamed: C7.1, L2.2, U$15.2 (LNA_IN)
unnamed: C9.1, L2.1, X1.FP
unnamed: R3.2, U$15.52 (XTAL_N)
unnamed: C17.1, U$15.53 (XTAL_P), Y1.3 (2)
unnamed: C18.1, R3.1, Y1.1
NEOPIX: LED1.1 (DI), U$15.43 (MTCK)
NEOPIX_PWR: LED1.2 (VDD), U$15.42 (IO38)
RX: JP3.1, JP3.1C (1), U$15.22 (XTAL_32K_N)
SCK: JP3.2, JP3.2C (2), U$15.40 (IO36)
SCL: JP1.6, JP1.6C (6), U$15.11 (IO6)
SCL1: CONN1.4 (SCL), U$15.44 (MTD0)
SDA: JP1.5, JP1.5C (5), U$15.12 (IO7)
SDA1: CONN1.3 (SDA), U$15.46 (MTDI)
TX: JP1.7, JP1.7C (7), U$15.10 (IO5)
VBAT: D2.A, VBAT0.P$1
VBUS: D1.A, X6.A4B9 (VBUS), X6.B4A9 (VBUS)
VDD3P3: L1.2, U$15.3 (VDD3P3@0), U$15.4 (VDD3P3@1)
VDD_SPI: C12.1, C13.1, U$15.30 (VDD_SPI)
~RESET: C3.1, Q2.A, Q2.A' (P1), R1.2, SWC1.TP, U$15.56 (CHIP_PU)

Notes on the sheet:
http://adafruit.com/products/xxx
Stemma QT
3.3V LDO
Headers
NeoPixel
USB Power/Data
Adafruit QT Py
CC 2.5 BY-SA
Fast SPI No ADC

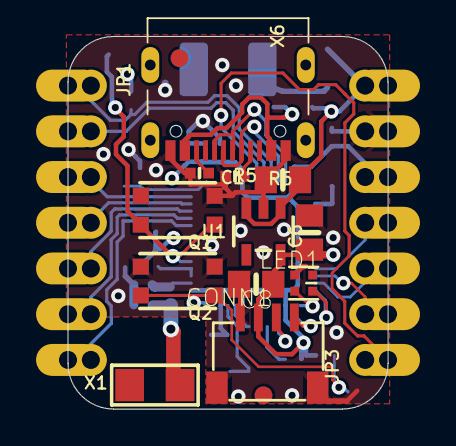
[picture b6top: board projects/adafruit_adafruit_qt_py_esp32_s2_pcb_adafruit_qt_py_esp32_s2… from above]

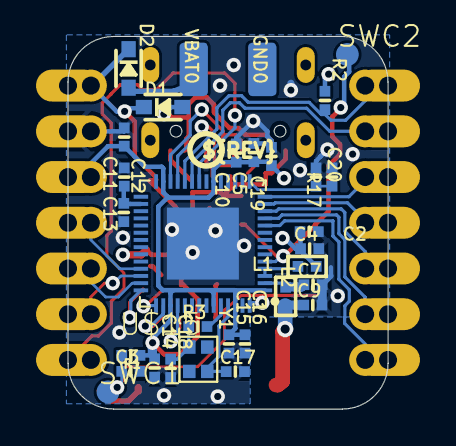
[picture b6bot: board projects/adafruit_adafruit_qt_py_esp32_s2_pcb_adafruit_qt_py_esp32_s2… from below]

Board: 4 copper layers, 17.8 x 20.7 mm, 50 parts (33 on the bottom side), 34 nets.

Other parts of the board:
U$7: QTPYS2_BOT
U$12: PCBFEAT-REV-040
U$13: QTPY_ESP32_TOP
